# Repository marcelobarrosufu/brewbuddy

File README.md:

# Description

BrewBuddy is a compact device for helping homebrewers in their exhausting task of converting malts, hops and yeasts into happiness.

It can be used as a simple thermometer, like any other analog thermometer found in the market but aggregating time control via stopwatch. As you know, time and temperature walk together when brewing a nice beer.

Although BrewBuddy is not a controller, you can program your recipe using a step mash strategy. BrewBuddy will blink a led when an step is finished, indicating that you can heat the mosture again.

When boiling, it is very easy to program your hop additions, waiting for a BrewBuddy indication. Smartphones or additional devices are not required anymore!

BrewBuddy is powered by a regular CR2032 battery, running for 20h! Menus and configurations are simple and intuitive, you will learn all function in minutes.

You can program up to 10 steps/hop additions (time) and the last setup is automatically saved in non volatile memory.

Some videos:

 - https://youtu.be/tlFAVe8KUfs
 - https://youtu.be/ZO_FSPlZCxY
 - https://youtu.be/FMSUGOILIN4
 - https://youtu.be/00Js_LpAEr8
 - https://youtu.be/yrWA2lQHpJ8

# Author

BrewBuddy was created from scracth by me, Marcelo Barros. I am an electrical engineer, professor and home brewer. After some bad experiences with uncalibrated analog thermometers I decided to create my own thermometer, agregating additional functionalities for mashing and boiling.

# Help Required

If you are a 3D expert and wanna help, please contact me. In the next week my new PCBs will arrive and I can ship  a complete and working board for those that want to develop or improve the current case.

# Compiling

 - Create a new workspace using System Worbenck for STM32 (SW4STM32). For instance,  <path>/brewbuddy
 - Go to brewbuddy directory and clone this repository
 - Starts SW4STM32 and import the project:   File->Import->General->Existing Projects into Workspace
 - In the dialog, please set:
    - Select root directory:  select your workspace directory, <path>/brewbuddy
    - Select the brew buddy project
    - Do not check the option "copy projects into workspace"
 - Before compiling, check optimization as "Optimize for Size (-Os)", under Properties->C/C++ Build->Tool Settings->MCU GCC Compiler->Optimization

# Firmware Notes

BrewBuddy firmware was built with low power requirements in mind, generating several actions:

 - The controller clock was reduced to 1MHz. Internal 8MHz clock (HSI) is used and PLL is disabled. 
 - I2C clock is only 100kHz (standard mode).
 - The main loop (see `main.c`) is only a _WFI (wake for interrupt) call, all code runs in interrupt mode:
   - Systick (1ms) timer is used to coordenate the periodic events (leds, display updates, ADC samplig and calibration). When some action is required, for instance a display update, it creates an event and sets SVD exception as pending. SVD is configured as a low priority exception, running only when other high priority interrupts are idle. This way we can ensure a better temporization for BrewBuddy.
  - Led modes were implemented as the amount of systick ticks for ON and OFF states. Using this strategy, the led processing is very light, taking few CPU time and energy.
  - Floating point is not used (less power and less flash requirements).
  
Some firmware notes:

  - As the battery voltage level is always falling I decided to calibrate the ADC periodically. DMA was not used to sampling the ADC values due the high cost in terms of flash usage. STM32 HAL takes some kBs of flash for DMA and a baremetal usage of DMA is required if we want to keep the flash usage low as possible. I need more time for this implementation. Or I need to use a microcontroller with bigger flash.
  - `bb_scr.c` is the main file for OLED screens. OLED screens are a machine state, in fact. Each screen is represented by a function (state) with the prototype `bb_scr_list_t bb_screen_function(bool first_time, bb_key_event_t *key)`, where:
    - `first_time`: it is used to indicate when we have a new screen to be presented or the same screen. Static text may be drawn in display using this flag, decreasing the amount of elements that need to be updated at each screen refresh.
    - `key`: if a key was pressed the information is here.
    - Remember: screens are implemented as a machine state (function based). So, you must return the next state when leaving the screen function. The list of states is given by the enumeration `bb_scr_list_t`. To include a new state, you must edit the macro `XMACRO_SCR_LIST`, adding a new state ID and a new function name, like `X(BB_SCR_NEW_OP_ID, bb_scr_new_op_boil)`. After, create a function for `bb_scr_new_op_boil` and implement the screen and your state changes based on the screen ID and keys pressed.
  - Step control is implemented in `ctrl.c`. Again, it is a machine state called at each 1s (see `ctrl_sm_run_1s()`). Given a proper initialization, steps can be followed by the states implemented in `ctrl.c`. 
  - All LMT86 handling was implemented in `lmt86.c`. Given the current temperature value (in ADC steps) and the amount of steps for a 2.5V reference, the real temperature (in degrees) is calculate (see `lmt86_conv_temp_1d()`). As we do not use floating point, conversion is based on a mV x degrees table (provided by datasheet). A simple interpolation is performed when the current value is not in the table. The temperature value is multiplied by ten for a minimum precision in integer operations.
  - If you want to change fonts, check the file `ssd1306_fonts.c`. We are using a small 7x5 font due to flash limits but it is possible to create bigger fonts and better presentation. The SSD1306 driver is minimal as well, a stripped/modified version of original driver provided by stm32f4-discovery.net. 
  - In `persist.c` you can find the default value for persistence and the routines to save / restore values from flash. A CRC is provided to check data integrity. The last flash sector (1kB) is used for data storage.
  
  At this moment, we do not have flash for anything else, even compiling for release and using size optimization:

| Flash | RAM (data+bss) |
| --- | --- |
| 15092 of 15360 bytes (98.3%) | 1200 of 4096 bytes (29.3%) |

# Adding localization support 

Some steps to add support for a new language:

  - Create a copy of `bb_locale_ENUS.h` and modify the suffix using a combination of [ISO-639 Language Codes and ISO ISO-3166 Country Codes](https://docs.oracle.com/cd/E13214_01/wli/docs92/xref/xqisocodes.html). For instance, you can use `bb_locale_ESCL.h` for Spanish and Chile.
  - Change the define `BB_DEFAULT_LOCALE` inside `bb_locale.h` (use your localization file name).
  - Translate the file contents. 
  - In special, for units, change `BB_TEMP_UNIT_IS_CELSIUS` and `BB_TEMP_UNIT_LABEL` for your corresponding temperature unit (0 and 'F' for Fahrenheit and 1 and 'C' for Celsius).

# CAD Files

Please, install KiCAD for opening schematics and PCB.

# TODO

 - When followings steps, make possible to go to next step without waiting the heating phase (just pressing RIGHT key)
 - Calibration menu
 - Setup menu, for temperatue and language
 - Change the microcontroller for more flash space (required for additional menus). STM32F030K6 or STM32F031F6 are possible options. The second one is more expensive but pin compatible.
 - Read internal temperature (for protection or calibration).
 - Low battery indication at startup.

# Licensing

BrewBuddy by Marcelo Barros de Almeida is licensed under a Creative Commons Attribution-NonCommercial-ShareAlike 4.0 International License.
If you want to create a commercial device based on BrewBuddy, please contact me for other licenses and prices.

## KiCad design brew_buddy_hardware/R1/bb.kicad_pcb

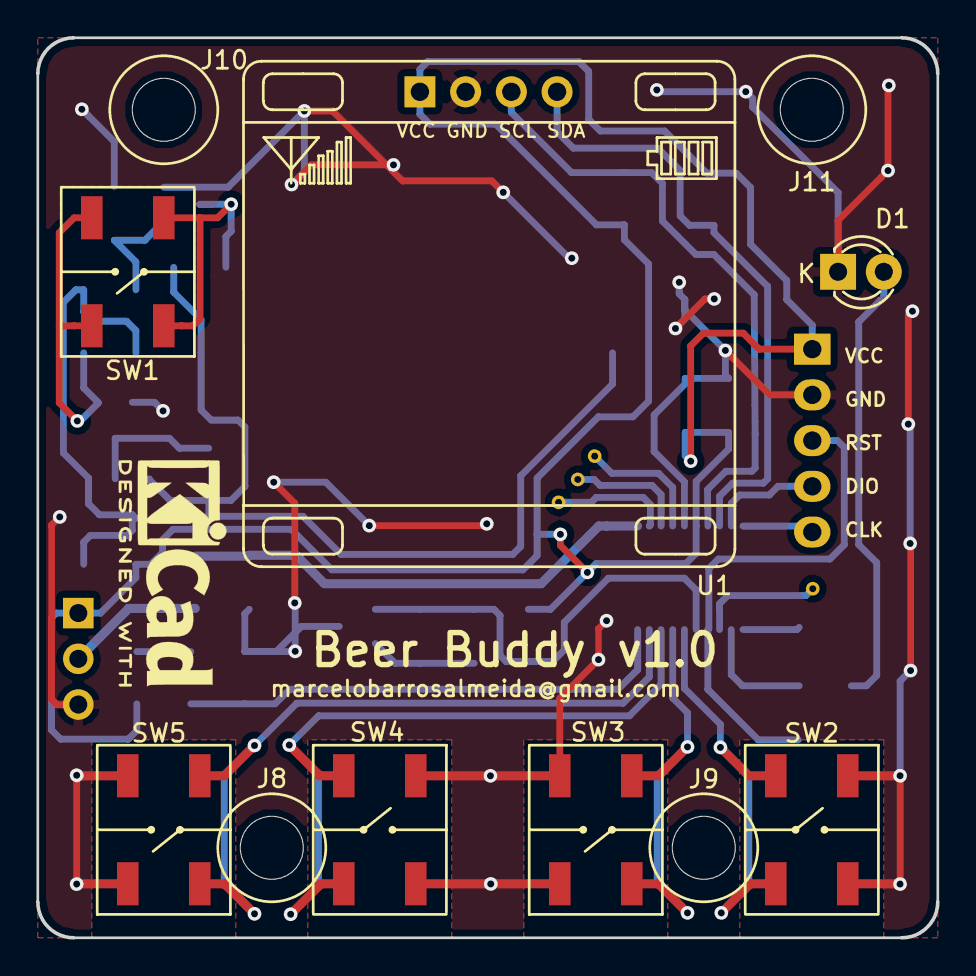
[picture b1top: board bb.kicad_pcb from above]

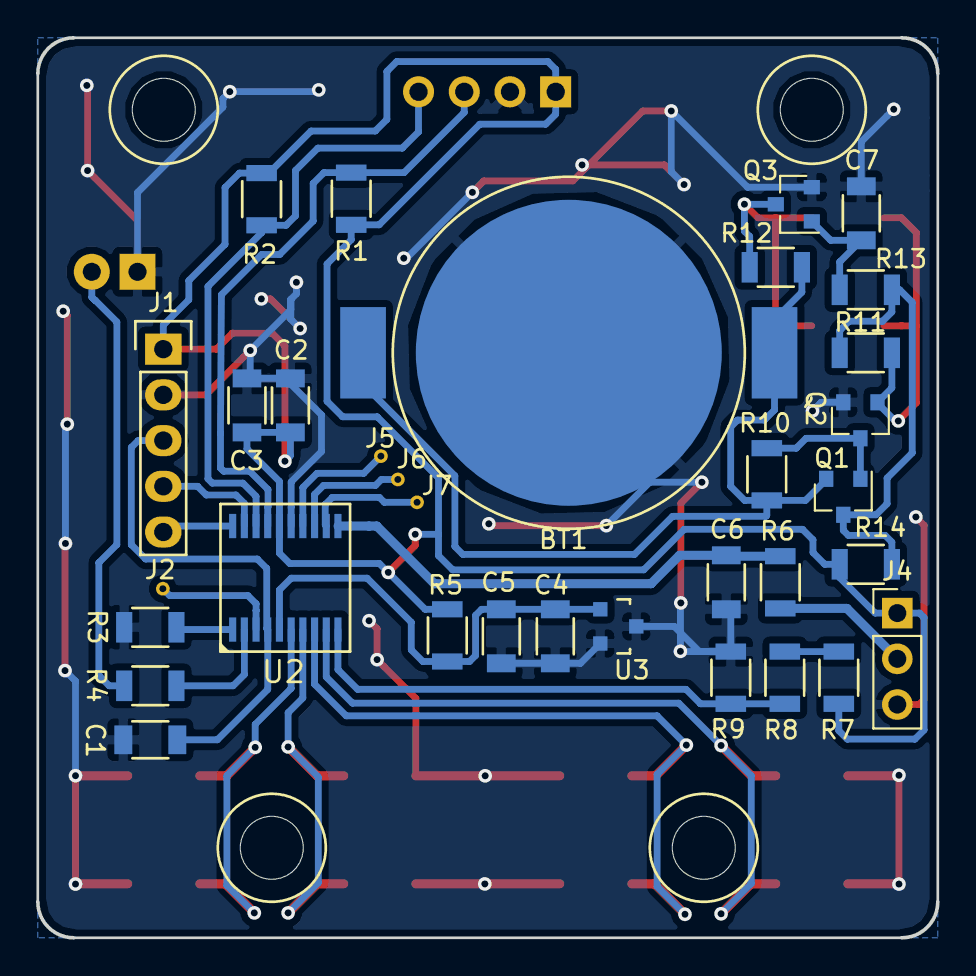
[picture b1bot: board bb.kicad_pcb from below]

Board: 2 copper layers, 50.0 x 50.0 mm, 44 parts (33 on the bottom side), 29 nets.

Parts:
BT1: CR2032; BAT-HLD-001-THM
C1, C2: 100nF; C_1206_CUSTOM
C3: 4.7uF; C_1206_CUSTOM
C4: 10nF; C_1206_CUSTOM
C5, C6: 1uF; C_1206_CUSTOM
C7: 22uF; C_1206_CUSTOM
D1: LED; LED-3MM
J1: JTAG; Pin_Header_Straight_1x05
J2: PF1; TEST-PIN
J4: Sensor; Pin_Header_Straight_1x03_Pitch2.54mm
J5: PA7; TEST-PIN
J6: PA6; TEST-PIN
J7: PA5; TEST-PIN
J8, J9, J10, J11: Drill; M3_Connector
Q1: PMV48XP (PMOS_GSD); SOT-23
Q2, Q3: PMV65UNER (NMOS_GSD); SOT-23
R1, R2, R6: 2K; R_1206_CUSTOM
R3: 10K; R_1206_CUSTOM
R4: 330R; R_1206_CUSTOM
R5: 3K; R_1206_CUSTOM
R7, R8: 30K; R_1206_CUSTOM
R9: 300K; R_1206_CUSTOM
R10, R11, R12: 100K; R_1206_CUSTOM
R13: 1M; R_1206_CUSTOM
R14: 0R; R_1206_CUSTOM
SW1, SW2, SW3, SW4, SW5: SW_SPST; EVQ-Q2B02W
U1: OLED-DISPLAY-I2C-128X64; DISPLAY-OLED
U2: STM32F030F4; TSOP-20-STM32F030F4
U3: ADR5041BRTZ; SOT-23

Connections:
/2V5BAT: R8.2, R9.1, U2.10
/2V5REF: C4.1, C5.1, R5.2, U2.5, U3.1
/ADC_TEMP: C6.1, R6.2, U2.11
/ALAM_LED: R4.1, U2.2
/NRST: C1.1, J1.3, U2.4
/SCL: R1.1, U1.3, U2.17
/SDA: R2.2, U1.4, U2.18
/SWCLK: J1.5, U2.20
/SWDIO: J1.4, U2.19
/SWDOWN: SW4.2, U2.8
/SWLEFT: SW3.2, U2.7
/SWRIGHT: SW2.2, U2.6
/SWUP: SW5.2, U2.9
BAT3V: Q1.3, R11.2, R13.2, R14.1
GND: BT1.2, C1.2, C2.2, C3.2, C4.2, C5.2, C6.2, C7.2, D1.1, J1.2, J4.3, Q2.2, Q3.2, R3.2, R9.2, SW2.1, SW3.1, SW4.1, SW5.1, U1.2, U2.15, U3.2, U3.3
unnamed: BT1.1, Q1.2, R10.2, R12.2
unnamed: C7.1, Q3.1, R13.1
unnamed: D1.2, R4.2
unnamed: J2.1, U2.3
unnamed: J4.2, R6.1
unnamed: J5.1, U2.14
unnamed: J6.1, U2.13
unnamed: J7.1, U2.12
unnamed: Q1.1, Q2.3, R10.1
unnamed: Q2.1, R11.1, SW1.1
unnamed: Q3.3, R12.1, SW1.2
unnamed: R3.1, U2.1
unnamed: R7.2, R8.1
VDD: C2.1, C3.1, J1.1, J4.1, R1.2, R2.1, R5.1, R7.1, R14.2, U1.1, U2.16

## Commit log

2018-01-03 adding ignore file
2018-01-03 first public version
2018-01-05 enhancing firmware notes
2018-01-05 Adding design files for case
2018-01-07 Adding more firmware detais
2018-08-05 fixing localization support and improving localization documentation
2018-08-05 fixing scale conversion bug

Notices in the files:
brew_buddy_hardware/R1/bb.kicad_pcb:
All rights reserved
